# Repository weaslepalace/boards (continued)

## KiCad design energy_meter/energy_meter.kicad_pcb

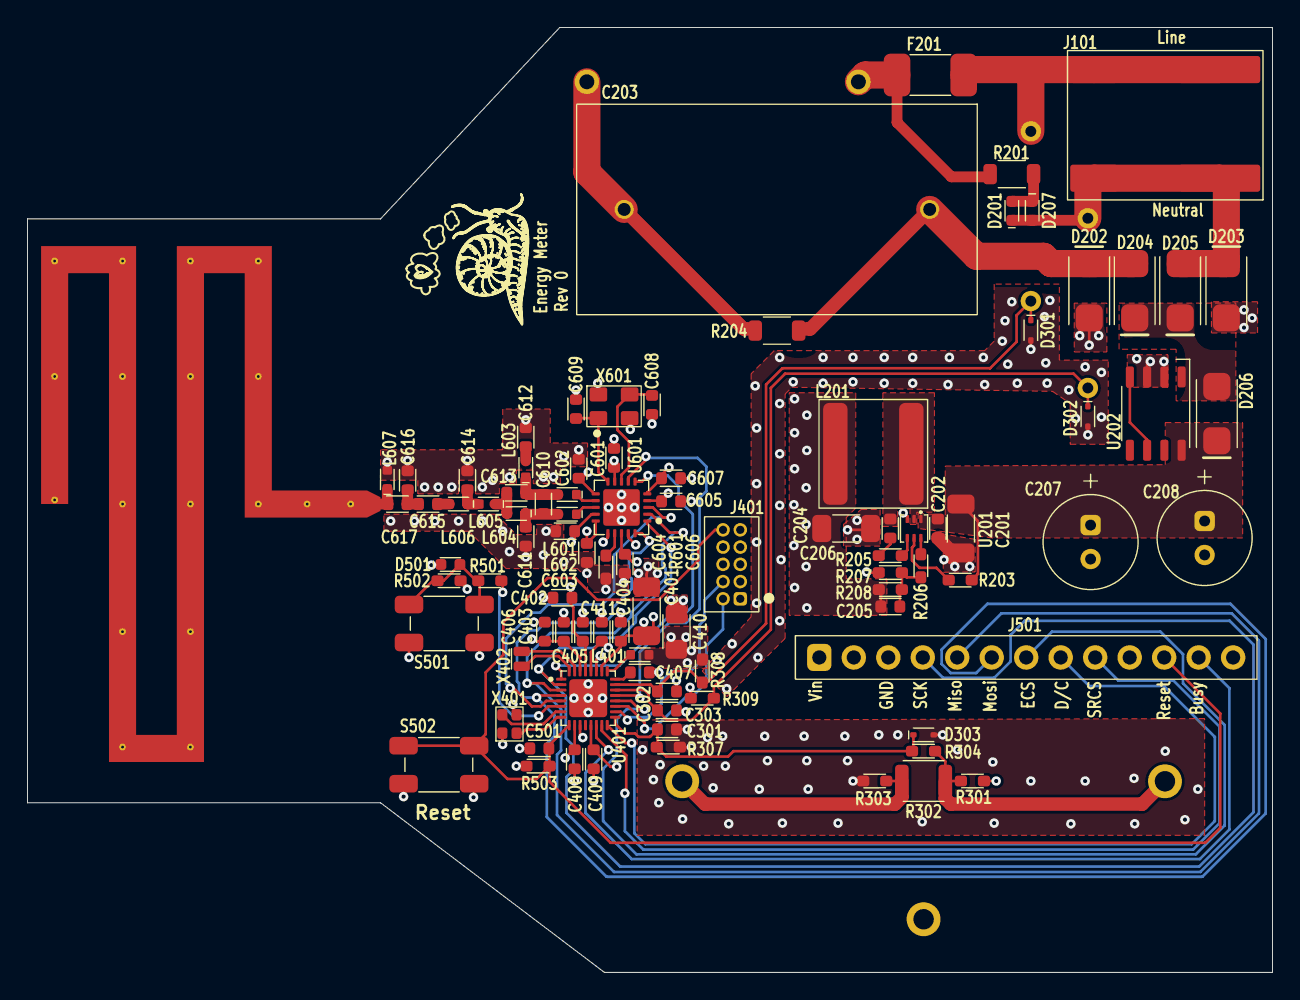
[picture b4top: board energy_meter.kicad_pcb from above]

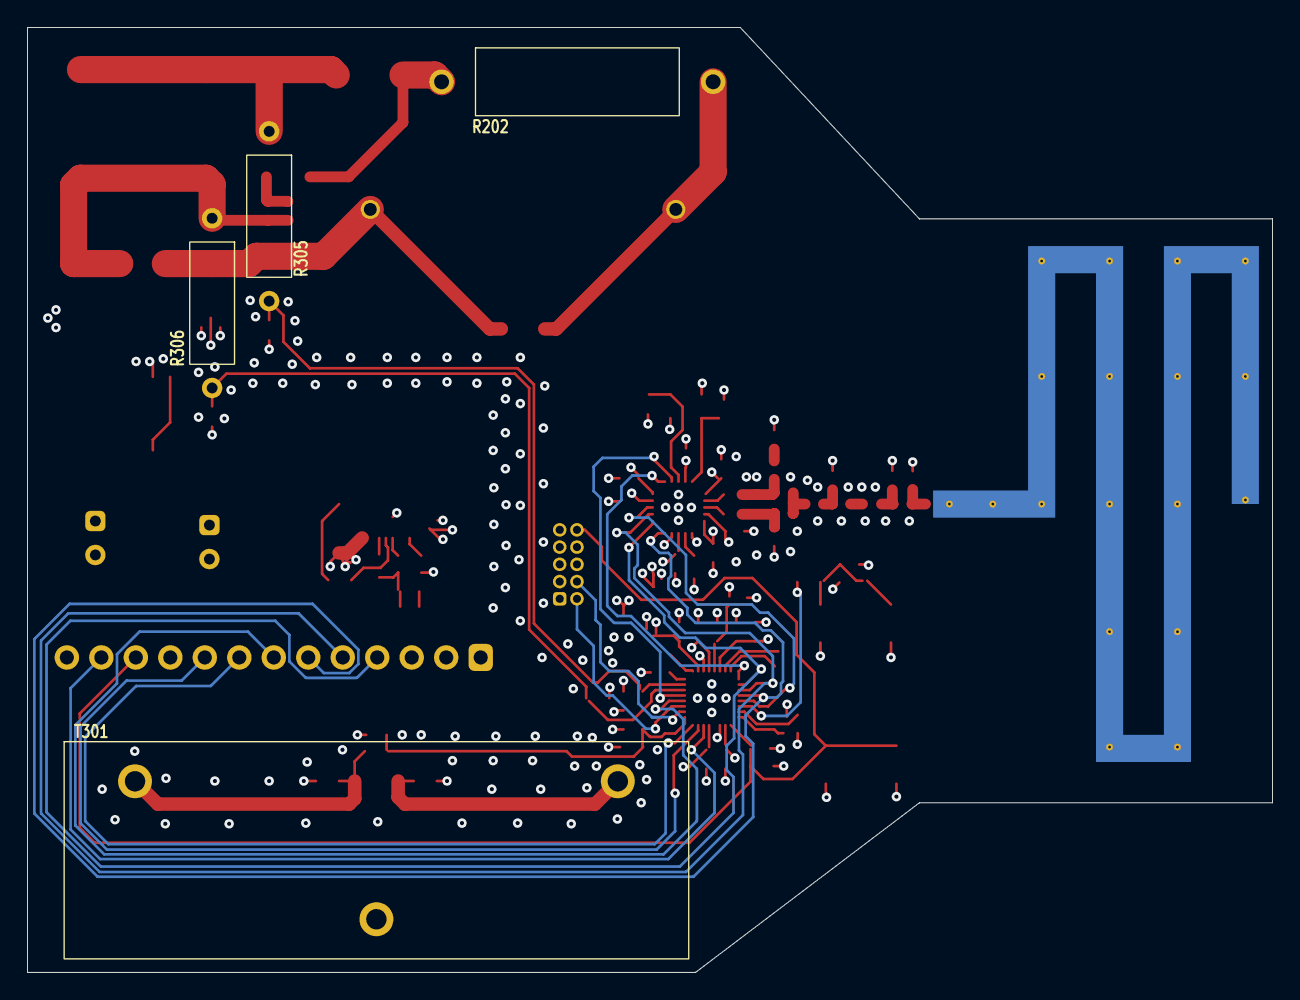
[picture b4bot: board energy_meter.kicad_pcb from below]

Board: 4 copper layers, 91.7 x 69.6 mm, 97 parts (4 on the bottom side), 57 nets.

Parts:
A601: TI_DN024_Single_Band
C201, C206, C401: 10uF; C_1206
C202, C404, C405, C406, C408, C409, C411, C501, C601, C602, C603, C604, C605, C606, C607: 100nF; C_0603
C203: 2.2uF; TDK_MPK_Polycap_22uF
C204, C402, C403, C407: 1uF; C_0603
C205, C608, C609: 15pF; C_0603
C207, C208: 220uF; Wurth_Radial_Cap_6.3MM
C301, C302, C303: 1nF; C_0603
C410: 4.7uF; C_0805
C610, C616, C617: 1pF; C_0603
C611, C613: 1.5pF; C_0603
C612, C615: 100pF; C_0603
C614: 3.3pF; C_0603
D201, D207, D501: Green; LiteOn_LED0603
D202, D203, D204, D205, D206: onsemi_DO-214AC
D301, D302, D303: onsemi_SOD523
F201: 2A; Bel_0679H
GFX101: Snaily
J101: WAGO_2060-852998-404
J401: Samtec_FTSH_10pin_Unshrouded
J501: Header_1x13
L201: L; Vishay_L_3131
L401: 2.2uH; L_0603
L601, L602, L605, L606, L607: 12nH; L_0603
L603, L604: 18nH; L_0603
R201, R204: 200k; R_1206
R202: 22; TE_NeohmRR
R203: 100k; R_0603
R205: 10; R_0603
R206: 82k; R_0603
R207, R503: 10k; R_0603
R208: 40.2k; R_0603
R301: 12k; R_0603
R302: 100; R_1210
R303: 62k; R_0603
R304: 3.3k; R_0603
R305, R306: 1.1M; Yageo_MRF50
R307: 20k; R_0603
R308, R309: 6.8k; R_0603
R501: 100; R_0603
R502: 1k; R_0603
R601: 56k; R_0603
S501, S502: CK_PTS810
T301: Telema_AC1100
U201: Monolithic_SOT563
U202: Microchip_SOIC_8
U401: SiLabs_VQFN32
U601: TI_QFN20_RGP
X401: 38.4MHz; ECS_ECX-1637B
X402: 32.768kHz; ECS_ECX-16
X601: 27MHz; Abracon_ABM8

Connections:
+1.8V: C302.1, C303.1, C408.1, C409.1, C410.2, C411.1, L401.2, R308.1, R309.1, U401.10 (DVDD), U401.13 (DVDD), U401.28 (DVDD)
+3V: C205.2, C206.1, C401.1, C402.1, C403.1, C404.1, C405.1, C406.1, C601.1, C602.1, C603.1, C604.1, C605.1, C606.1, C607.1, J401.1 (Vref), J501.1 (VIN), L201.2, R208.2, R301.1, R502.1, R503.1, U401.26 (VREGVDD), U401.29 (AVDD), U401.30 (IOVDD), U601.4 (DVDD), U601.5 (DCOUPL), U601.9 (AVDD), U601.11 (AVDD), U601.14 (AVDD), U601.15 (AVDD), U601.18 (DGUARD)
/HMI.Busy: J501.12 (BUSY), U401.14 (PB02)
/HMI.DC: J501.8 (D/C), U401.16 (PB00)
/HMI.ECS: J501.7 (ECS), U401.20 (PA03/SWO)
/HMI.LED: R501.1, U401.6 (PC05)
/HMI.Reset: C501.1, J401.10 (~RESET), J501.11 (RST), R503.2, S502.1, U401.9 (~RESET)
/HMI.SRCS: J501.9 (SRCS), U401.15 (PB01)
/Microcontroller/Sense.Current: C301.1, D303.1 (K), R304.2, R307.1, U401.17 (PA00)
/Microcontroller/Sense.Line: C302.2, D301.1 (K), R305.2, R308.2, U401.23 (PA06)
/Microcontroller/Sense.Neutral: C303.2, D302.1 (K), R306.2, R309.2, U401.22 (PA05)
/Power/12V,50mA: C201.1, C202.1, C207.1, C208.1, D206.1 (K), R203.1, U201.1 (VIN), U202.8 (OUT)
/Power/AC.Line: F201.1, J101.1, J101.3, R305.1
/Power/AC.Neutral: D201.1 (K), D203.1 (K), D205.2 (A), D207.2 (A), J101.2, J101.4, R306.1
/Radio.CS: U401.21 (PA04), U601.7 (~CS)
/Radio.GDO0: U401.1 (PC00), U601.6 (GDO0)
/Radio.GDO2: U401.5 (PC04), U601.3 (GDO2)
/SPI.Miso: J501.5 (MISO), U401.3 (PC02), U601.2 (S0)
/SPI.Mosi: J501.6 (MOSI), U401.4 (PC03), U601.20 (SI)
/SPI.SCK: J501.4 (SCK), U401.2 (PC01), U601.1 (SLCK)
GND: C201.2, C202.2, C206.2, C207.2, C208.2, C301.2, C401.2, C402.2, C403.2, C404.2, C405.2, C406.2, C407.2, C408.2, C409.2, C410.1, C411.2, C501.2, C601.2, C602.2, C603.2, C604.2, C605.2, C606.2, C607.2, C608.2, C609.2, C611.1, C612.2, C614.2, C616.2, D202.2 (A), D203.2 (A), D301.2 (A), D302.2 (A), D303.2 (A), D501.1 (K), J401.3 (GND), J401.5 (GND), J501.3 (GND), L607.2, R207.2, R303.2, R307.2, R601.2, S501.2, S502.2, U201.3 (GND), U202.2 (PGND), U202.3 (AGND), U401.0 (VSS), U401.11 (VSS), U401.27 (VREGVSS), U601.0 (GND), U601.16 (GND), U601.19 (GND), X401.2, X401.4 (GND), X601.2, X601.4 (GND)
unnamed: A601.1, C617.2, L607.1
unnamed: C203.1, R202.2, R204.1
unnamed: C204.1, R205.2
unnamed: C205.1, R206.2, R207.1, R208.1
unnamed: C610.1, C613.1, L601.2, L603.1
unnamed: C610.2, C611.2, L602.2, L604.1
unnamed: C612.1, L603.2
unnamed: C613.2, L604.2, L605.1
unnamed: C614.1, L605.2, L606.1
unnamed: C615.1, L606.2
unnamed: C615.2, C616.1, C617.1
unnamed: D201.2 (A), D207.1 (K), R201.2
unnamed: C203.2, D202.1 (K), D204.2 (A), R204.2
unnamed: D204.1 (K), D205.1 (K), D206.2 (A), U202.1 (SH)
unnamed: D501.2 (A), R501.2, R502.2, S501.1
unnamed: F201.2, R201.1, R202.1
unnamed: J401.4 (SWCLK), U401.18 (PA01/SWCLK)
unnamed: J401.2 (SWDIO), U401.19 (PA02/SCWIO)
unnamed: R301.2, R302.1, R304.1, T301.1
unnamed: R302.2, R303.1, T301.2
unnamed: R205.1, U201.4 (BST)
unnamed: R203.2, U201.5 (EN)
unnamed: R206.1, U201.6 (FB)
unnamed: C204.2, L201.1, U201.2 (SW)
unnamed: U202.4 (FB), U202.6 (D12)
unnamed: C407.1, U401.24 (DECOUPLE)
unnamed: U401.7 (HFXTAL_I), X401.3
unnamed: U401.8 (HFXTAL_O), X401.1
unnamed: U401.32 (PD00/LFXTAL_O), X402.2
unnamed: U401.31 (PD01/LFXTAL_I), X402.1
unnamed: L401.1, U401.25 (VREGSW)
unnamed: R601.1, U601.17 (RBIAS)
unnamed: L602.1, U601.13 (RF_N)
unnamed: L601.1, U601.12 (RF_P)
unnamed: C608.1, U601.8 (XOSC_Q1), X601.3
unnamed: C609.1, U601.10 (XOSC_Q2), X601.1

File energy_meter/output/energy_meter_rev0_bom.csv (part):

"Reference","Value","Qty","DNP","Manufacturer","Manufacturer Part Number","Supplier","Supplier Part Number","Description"
"C201,C206,C401","10uF","3","","Samsung Electro-Mechanics","CL31B106KAHNFNE","Digikey","1276-3100-2-ND","10 µF ±10% 25V Ceramic Capacitor X7R 1206 (3216 Metric)"
"C202,C404,C405,C406,C408,C409,C411,C501,C601,C602,C603,C604,C605,C606,C607","100nF","15","","Murata Electronics","GCJ188R72A104KA01D","Digikey","490-13420-2-ND","0.1 uF ±10% 100V Ceramic Capacitor X7R 0603 (1608 Metric)"
"C203","2.2uF","1","","EPCOS - TDK Electronics","B32923P3225K000","Digikey","495-B32923P3225K000-ND","2.2 µF Film Capacitor 305V 630V Polypropylene (PP) Radial"
"C204,C402,C403,C407","1uF","4","","Murata Electronics","GCJ188R71E105KA01D","Digikey","490-14409-2-ND","1 uF ±10% 25V Ceramic Capacitor X7R 0603 (1608 Metric)"
"C205,C608,C609","15pF","3","","Murata Electronics","GCM1885C2A150FA16D","Digikey","490-16416-2-ND","15 pF ±1% 100V Ceramic Capacitor C0G, NP0 0603 (1608 Metric)"
"C207,C208","220uF","2","","Würth Elektronik","860010473011","Digikey","732-8634-1-ND","220 µF 25 V Aluminum Electrolytic Capacitors Radial, Can 2000 Hrs @ 85°C"
"C301,C302,C303","1nF","3","","Murata Electronics","GRM1885C1H102JA01D","Digikey","490-1451-2-ND","1000 pF ±5% 50V Ceramic Capacitor C0G, NP0 0603 (1608 Metric)"
"C410","4.7uF","1","","Samsung Electro-Mechanics","CL21B475KOFNFNE","Digikey","1276-2970-2-ND","4.7 µF ±10% 16V Ceramic Capacitor X7R 0805 (2012 Metric)"
"C610,C617","1pF","2","","Murata Electronics","GCM1885C2A1R0CA16D","Digikey","490-GCM1885C2A1R0CA16DTR-ND","1 pF ±0.25pF 100V Ceramic Capacitor C0G, NP0 0603 (1608 Metric)"
"C611,C613","1.5pF","2","","Murata Electronics","GCM1885C2A1R5BA16D","Digikey","490-GCM1885C2A1R5BA16DTR-ND","1.5 pF ±0.1pF 100V Ceramic Capacitor C0G, NP0 0603 (1608 Metric)"
"C612,C615","100pF","2","","Murata Electronics","GCM1885C2A101JA16D","Digikey","490-4771-2-ND","100 pF ±5% 100V Ceramic Capacitor C0G, NP0 0603 (1608 Metric)"
"C614","3.3pF","1","","Murata Electronics","GCM1885C2A3R3CA16D","Digikey","490-GCM1885C2A3R3CA16DTR-ND","3.3 pF ±0.25pF 100V Ceramic Capacitor C0G, NP0 0603 (1608 Metric)"
"C616","1pF","1","DNP","Murata Electronics","GCM1885C2A1R0CA16D","Digikey","490-GCM1885C2A1R0CA16DTR-ND","1 pF ±0.25pF 100V Ceramic Capacitor C0G, NP0 0603 (1608 Metric)"
"D201,D207,D501","Green","3","","Lite-On Inc.","LTST-C190GKT","Digikey","160-1183-2-ND","Green 569nm LED Indication - Discrete 2.1V 0603 (1608 Metric)"
"D202,D203,D204,D205,D206","~","5","","onsemi","MRA4004T3G","Digikey","MRA4004T3GOSTR-ND","Diode 400 V 1A Surface Mount SMA"
"D301,D302,D303","~","3","","onsemi","RB520S30T1G","Digikey","RB520S30T1GOSTR-ND","Diode 30 V 200mA Surface Mount SOD-523"
"F201","2A","1","","Bel Fuse Inc.","0679H2000-05","Digikey","5923-0679H2000-05TR-ND","2 A 350 V AC 72 V DC Fuse Board Mount (Cartridge Style Excluded) Surface Mount 2-SMD, Square End Block"
"J101","~","1","","WAGO Corporation","2060-852/998-404","Digikey","2946-2060-852/998-404TR-ND","2 Position Wire to Board Terminal Block Horizontal with Board 0.315"" (8.00mm) Surface Mount"
"J401","~","1","","Samtec Inc.","FTSH-105-01-F-D","Digikey","SAM9430-ND","Connector Header Through Hole 10 position 0.050"" (1.27mm)"
"J501","~","1","","Adam Tech","PH1-13-UA","DIgikey","2057-PH1-13-UA-ND","Connector Header Through Hole 13 position 0.100"" (2.54mm)"
"L201","L","1","","Vishay Dale","IFSC3232DBER330M01","Digikey","541-IFSC3232DBER330M01TR-ND","33 µH Shielded Wirewound Inductor 1.7 A 100mOhm 3131 (8080 Metric)"
"L401","2.2uH","1","","Murata Electronics","LQM18PZ2R2MFHD","Digikey","490-15982-2-ND","2.2 µH Shielded Multilayer Inductor 700 mA 470mOhm Max 0603 (1608 Metric)"
"L601,L602,L605,L606,L607","12nH","5","","Murata Electronics","LQG18HN12NJ00D","Digikey","490-6575-2-ND","12 nH Unshielded Multilayer Inductor 600 mA 350mOhm Max 0603 (1608 Metric)"
"L603,L604","18nH","2","","Murata Electronics","LQG18HN18NJ00D","Digikey","490-6577-2-ND","18 nH Unshielded Multilayer Inductor 600 mA 450mOhm Max 0603 (1608 Metric)"
"R201,R204","200k","2","","YAGEO","RC1206FR-07200KL","Digikey","311-200KFRTR-ND","200 kOhms ±1% 0.25W, 1/4W Chip Resistor 1206 (3216 Metric) Moisture Resistant Thick Film"
"R202","22","1","","TE Connectivity Passive Product","RR03J22RTB","Digikey","A131649CT-ND","22 Ohms ±5% 3W Through Hole Resistor Axial Flame Retardant Coating, Pulse Withstanding, Safety Metal Film"
"R203","100k","1","","YAGEO","RC0603FR-07100KL","Digikey","311-100KHRTR-ND","100 kOhms ±1% 0.1W, 1/10W Chip Resistor 0603 (1608 Metric) Moisture Resistant Thick Film"
"R205","10","1","","YAGEO","RC0603FR-0710RL","Digikey","311-10.0HRTR-ND","10 Ohms ±1% 0.1W, 1/10W Chip Resistor 0603 (1608 Metric) Moisture Resistant Thick Film"
"R206","82k","1","","YAGEO","RC0603FR-0782KL","Digikey","311-82.0KHRTR-ND","82 kOhms ±1% 0.1W, 1/10W Chip Resistor 0603 (1608 Metric) Moisture Resistant Thick Film"
"R207,R503","10k","2","","YAGEO","RC0603FR-0710KL","Digikey","311-10.0KHRTR-ND","10 kOhms ±1% 0.1W, 1/10W Chip Resistor 0603 (1608 Metric) Moisture Resistant Thick Film"
"R208","40.2k","1","","YAGEO","RC0603FR-0740K2L","Digikey","311-40.2KHRTR-ND","40.2 kOhms ±1% 0.1W, 1/10W Chip Resistor 0603 (1608 Metric) Moisture Resistant Thick Film"
"R301","12k","1","","YAGEO","RC0603FR-0712KL","Digikey","311-12.0KHRTR-ND","12 kOhms ±1% 0.1W, 1/10W Chip Resistor 0603 (1608 Metric) Moisture Resistant Thick Film"
"R302","100","1","","YAGEO","AC1210FR-7W100RL","Digikey","13-AC1210FR-7W100RLTR-ND","100 Ohms ±1% 1W Chip Resistor 1210 (3225 Metric) Automotive AEC-Q200, Moisture Resistant Thick Film"
"R303","62k","1","","YAGEO","RC0603FR-0762KL","Digikey","311-62.0KHRTR-ND","62 kOhms ±1% 0.1W, 1/10W Chip Resistor 0603 (1608 Metric) Moisture Resistant Thick Film"
"R304","3.3k","1","","YAGEO","RC0603FR-073K3L","Digikey","311-3.30KHRTR-ND","3.3 kOhms ±1% 0.1W, 1/10W Chip Resistor 0603 (1608 Metric) Moisture Resistant Thick Film"
"R305,R306","1.1M","2","","YAGEO","MFR50SFTE52-1M1","Digikey","13-MFR50SFTE52-1M1CT-ND","1.1 MOhms ±1% 0.5W, 1/2W Through Hole Resistor Axial Metal Film"
"R307","20k","1","","YAGEO","RC0603FR-0720KL","Digikey","311-20.0KHRTR-ND","~20 kOhms ±1% 0.1W, 1/10W Chip Resistor 0603 (1608 Metric) Moisture Resistant Thick Film"
"R308,R309","6.8k","2","","YAGEO","RC0603FR-076K8L","Digikey","311-6.80KHRTR-ND","6.8 kOhms ±1% 0.1W, 1/10W Chip Resistor 0603 (1608 Metric) Moisture Resistant Thick Film"
"R501","100","1","","YAGEO","RC0603FR-07100RL","Digikey","311-100HRTR-ND","100 Ohms ±1% 0.1W, 1/10W Chip Resistor 0603 (1608 Metric) Moisture Resistant Thick Film"
"R502","1k","1","","YAGEO","RC0603FR-071KL","Digikey","311-1.00KHRTR-ND","1 kOhms ±1% 0.1W, 1/10W Chip Resistor 0603 (1608 Metric) Moisture Resistant Thick Film"
"R601","56k","1","","YAGEO","RC0603FR-0756KL","Digikey","311-56KHRTR-ND","56 kOhms ±1% 0.1W, 1/10W Chip Resistor 0603 (1608 Metric) Moisture Resistant Thick Film"
"S501,S502","~","2","","C&K","PTS810SJG250SMTR LFS","Digikey","CKN10504TR-ND","Tactile Switch SPST-NO Top Actuated Surface Mount"
"T301","~","1","","Talema Group LLC","AC1100","Digikey","1295-AC1100-ND","100 A Current Sense Transformer 50/60Hz 21.3Ohm Through Hole"
"U201","~","1","","Monolithic Power Systems Inc.","MP1653AGTF-Z","Digikey","1589-MP1653AGTF-ZTR-ND",""
"U202","~","1","","Microchip Technology","SR10LG-G","Digikey","SR10LG-GTR-ND","Converter Offline Shunt Topology 50Hz ~ 60Hz 8-SOIC"
"U401","~","1","","Silicon Labs","EFM32PG22C200F64IM32-C","Digikey","336-EFM32PG22C200F64IM32-C-ND","ARM® Cortex®-M33 Gecko Microcontroller IC 32-Bit Single-Core 76.8MHz 64KB (64K x 8) FLASH 32-QFN (4x4)"
"U601","~","1","","Texas Instruments","CC110LRGPR","Digikey","296-35719-2-ND","IC RF TxRx Only General ISM < 1GHz 300MHz ~ 348MHz, 387MHz ~ 464MHz, 779MHz ~ 928MHz 20-VFQFN Exposed Pad"
"X401","38.4MHz","1","","ECS Inc.","ECS-384-10-37B-CTP-TR3","Digikey","50-ECS-384-10-37B-CTP-TR3TR-ND","38.4 MHz ±10ppm Crystal 10pF 50 Ohms 4-SMD, No Lead"
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
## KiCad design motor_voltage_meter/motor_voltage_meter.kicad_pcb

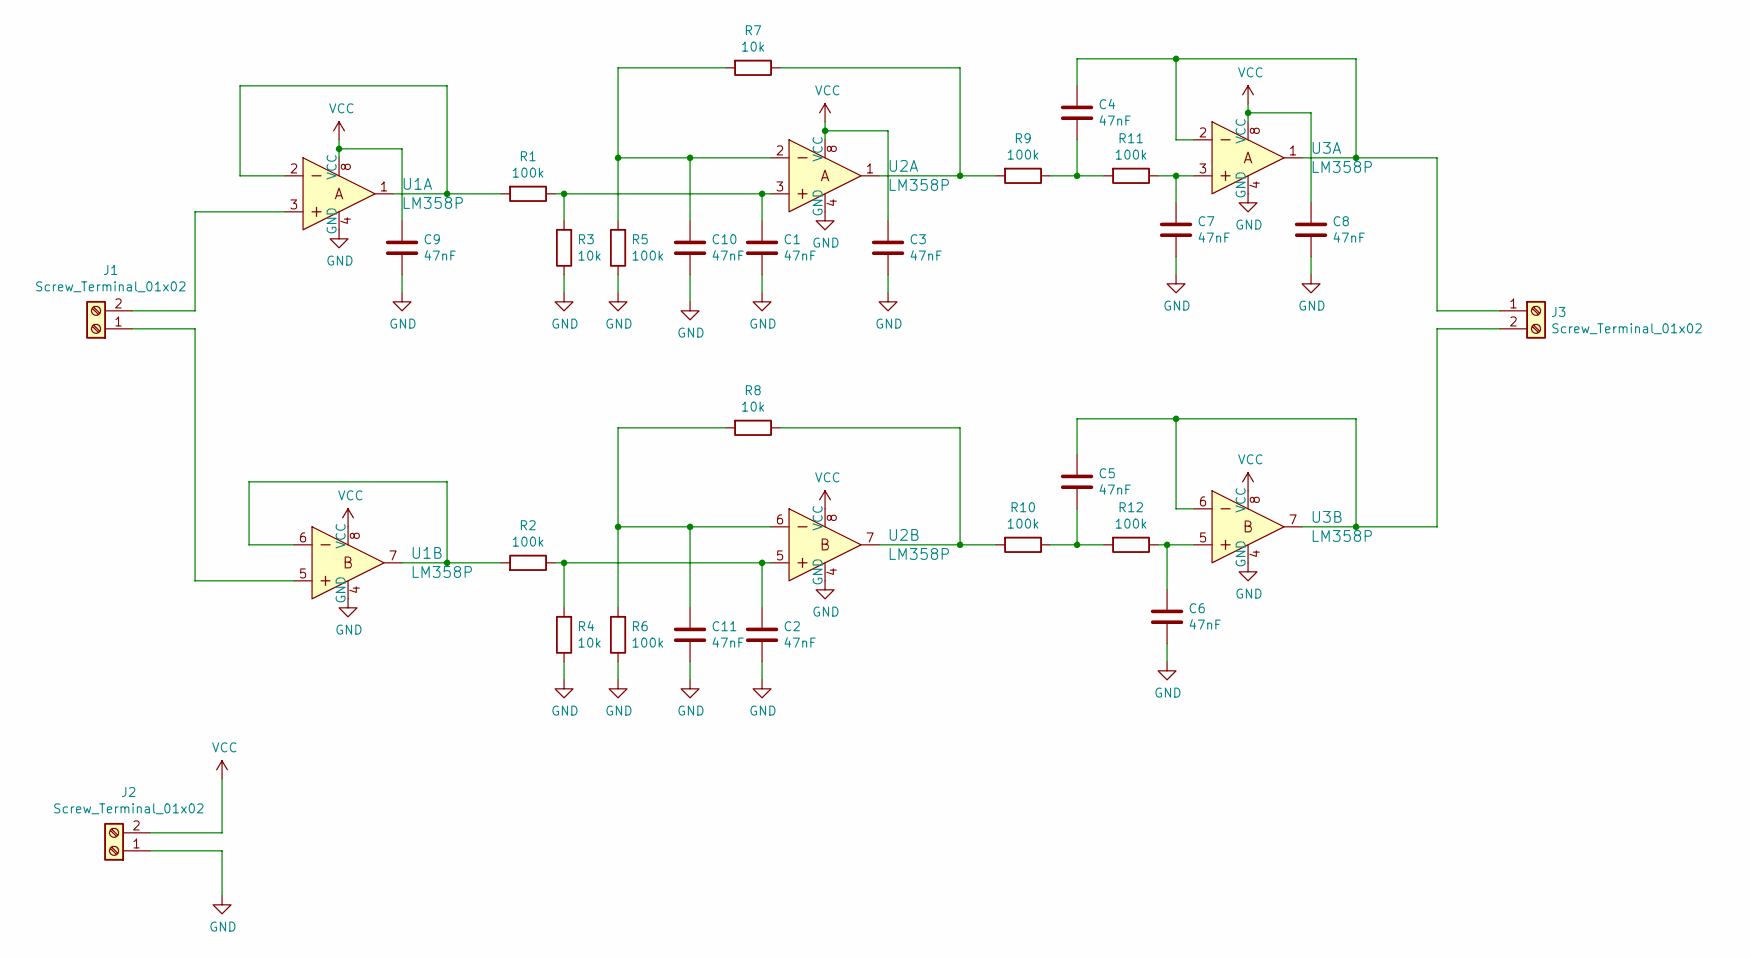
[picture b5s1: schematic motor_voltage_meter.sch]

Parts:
C1, C2, C3, C4, C5, C6, C7, C8, C9: 47nF; C_Rect_L7.0mm_W2.0mm_P5.00mm
C10, C11: 47nF
J1, J2, J3: Screw_Terminal_01x02; PinHeader_1x02_P2.54mm_Vertical
R1, R2, R5, R6, R9, R10: 100k; R_Axial_DIN0207_L6.3mm_D2.5mm_P7.62mm_Horizontal
R3, R7, R8: 10k; R_Axial_DIN0207_L6.3mm_D2.5mm_P2.54mm_Vertical
R4: 10k; R_Axial_DIN0207_L6.3mm_D2.5mm_P7.62mm_Horizontal
R11, R12: 100k; R_Axial_DIN0207_L6.3mm_D2.5mm_P2.54mm_Vertical
U1, U2, U3: LM358P; DIP-8_W7.62mm; MPN LM358P; Digi-Key_PN 296-1395-5-ND

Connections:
GND: C1.2, C2.2, C3.2, C6.2, C7.2, C8.2, C9.2, C10.2, C11.2, J2.1, R3.1, R4.1, R5.1, R6.1, U1.4 (GND), U2.4 (GND), U3.4 (GND)
unnamed: C1.1, R1.1, R3.2, U2.3
unnamed: C2.1, R2.1, R4.2, U2.5
unnamed: C4.1, J3.1, U3.1, U3.2
unnamed: C4.2, R9.1, R11.2
unnamed: C5.1, J3.2, U3.6, U3.7
unnamed: C5.2, R10.1, R12.2
unnamed: C6.1, R12.1, U3.5
unnamed: C7.1, R11.1, U3.3
unnamed: C10.1, R5.2, R7.2, U2.2
unnamed: C11.1, R6.2, R8.2, U2.6
unnamed: J1.1, U1.5
unnamed: J1.2, U1.3
unnamed: R1.2, U1.1, U1.2
unnamed: R2.2, U1.6, U1.7
unnamed: R7.1, R9.2, U2.1
unnamed: R8.1, R10.2, U2.7
VCC: C3.1, C8.1, C9.1, J2.2, U1.8 (VCC), U2.8 (VCC), U3.8 (VCC)

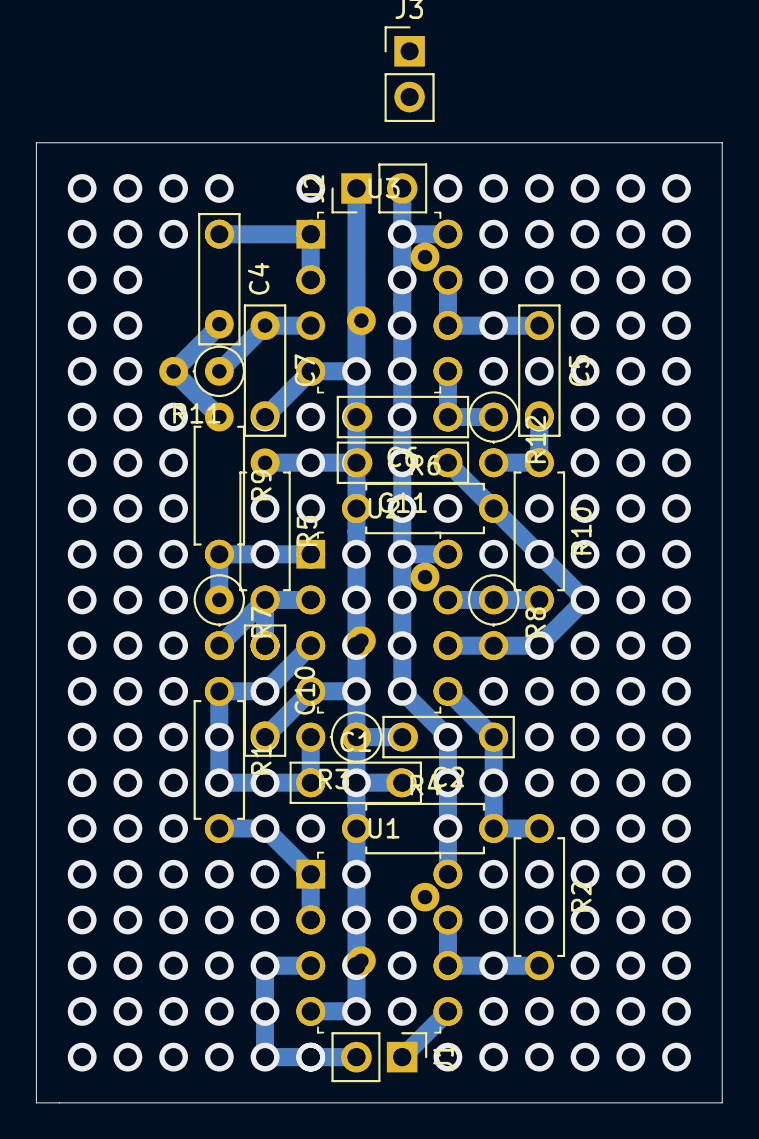
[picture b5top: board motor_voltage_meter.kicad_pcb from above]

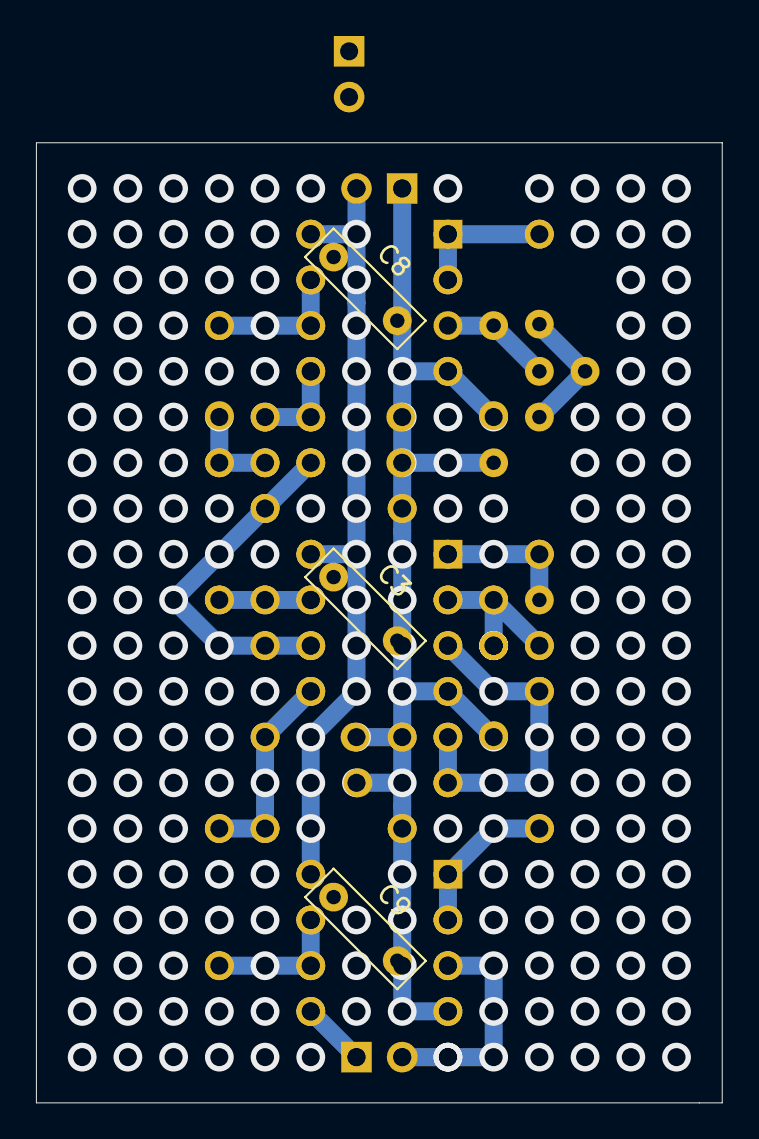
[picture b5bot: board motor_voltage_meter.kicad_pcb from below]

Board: 2 copper layers, 38.1 x 53.3 mm, 29 parts (3 on the bottom side), 18 nets.

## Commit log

2024-11-26 Initial
2024-12-03 Added library components for Energy Meter
2024-12-14 Board ready to order
2024-12-16 Created build outputs for energy-meter rev0
2025-01-13 Syncd EFM32s
2025-12-31 Commit December 31st, 2025
2026-01-15 Commit January 14th, 2026
2026-05-02 Added The_R0603_Library containing full YAGEO R0603 E96 family.
2026-05-05 Added The_C0603_Library with Murata GCM188 family of capacitors
